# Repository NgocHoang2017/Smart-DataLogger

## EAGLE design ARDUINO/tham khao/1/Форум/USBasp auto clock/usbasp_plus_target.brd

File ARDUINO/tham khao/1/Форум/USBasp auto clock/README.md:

## USBasp with Automatic Software Controlled Clock
---

### Informasi

* __fusebits.txt__ - Pengaturan fusebit untuk ATmega8 untuk USBasp.
* __firmaware.hex__ - Automatic Software Controlled Clock Jumper Free USBasp ATmega8.
* __usbasp_plus_target.sch__ - Skematik untuk USBasp.
* __usbasp_plus_target.brd__ - Layout untuk board USBasp.

### Catatan

* Firmware yang digunakan adalah __Automatic software controlled clock__ sehingga tidak perlu melakukan pengaturan __Low SCK__ lagi.
* Pada layout board USBasp ini terdapat sebuah jalur yang _unrouted_. Cukup abaikan jalur tersebut, karena memang tidak digunakan.
* Board ini telah melalui proses pengujian, dan berfungsi sesuai dengan yang diharapkan.

### Referensi

* [USBasp - USB programmer for Atmel AVR controllers](http://www.fischl.de/usbasp/)
* [Automatic Software Controlled Clock Jumper Free USBasp](https://automasys.wordpress.com/2013/02/16/%D9%BE%D8%B1%D9%88%DA%98%D9%87-%D8%A7%D9%84%DA%A9%D8%AA%D8%B1%D9%88%D9%86%DB%8C%DA%A9-avr-usbasp/)

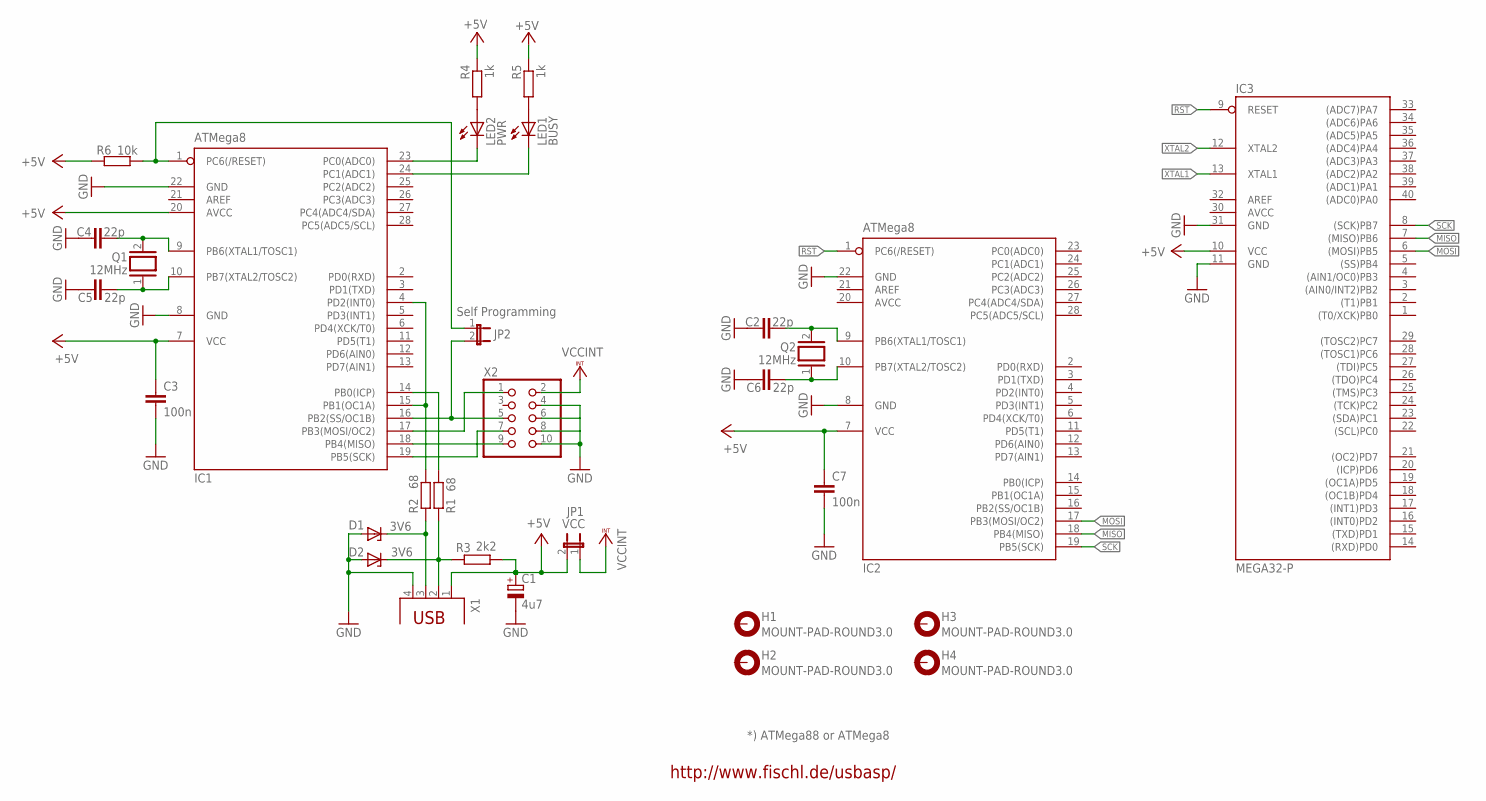
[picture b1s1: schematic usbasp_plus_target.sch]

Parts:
C1: 4u7; E2,5-5
C2, C4, C5, C6: 22p; C025-024X044
C3, C7: 100n; C025-024X044
D1, D2: 3V6; DO34Z7
H1, H2, H3, H4: MOUNT-PAD-ROUND3.0; 3,0-PAD
IC1, IC2: ATMega8; DIL28-3
IC3: MEGA32-P; DIL40
JP1: VCC; JP1
JP2: Self Programming; JP1
LED1: BUSY; LED3MM
LED2: PWR; LED3MM
Q1, Q2: 12MHz; QS
R1, R2: 68; 0204_7
R3: 2k2; 0204_7
R4, R5: 1k; 0204_7
R6: 10k; 0204_7
X1: PN61729
X2: PINHD-2X5; 2X05

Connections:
+5V: C1.+, C3.1, C7.1, IC1.7 (VCC), IC1.20 (AVCC), IC2.7 (VCC), IC3.10 (VCC), JP1.2, R3.1, R4.1, R5.1, R6.1, X1.1
AVCC: IC2.20 (AVCC), IC3.30 (AVCC)
GND: C1.-, C2.1, C3.2, C4.1, C5.1, C6.1, C7.2, D1.A, D2.A, IC1.8 (GND), IC1.22 (GND), IC2.8 (GND), IC2.22 (GND), IC3.11 (GND), IC3.31 (GND), X1.4, X2.4, X2.6, X2.8, X2.10
MISO: IC1.18 (PB4(MISO)), IC2.18 (PB4(MISO)), IC3.7 ((MISO)PB6), X2.9
MOSI: IC1.17 (PB3(MOSI/OC2)), IC2.17 (PB3(MOSI/OC2)), IC3.6 ((MOSI)PB5), X2.1
unnamed: IC1.1 (PC6(/RESET)), JP2.1, R6.2
unnamed: D2.C, R1.1, R3.2, X1.2
unnamed: IC1.4 (PD2(INT0)), IC1.15 (PB1(OC1A)), R2.2
unnamed: D1.C, R2.1, X1.3
unnamed: LED2.A, R4.2
unnamed: IC1.23 (PC0(ADC0)), LED2.K (C)
unnamed: IC1.24 (PC1(ADC1)), LED1.K (C)
unnamed: IC1.14 (PB0(ICP)), R1.2
unnamed: C4.2, IC1.9 (PB6(XTAL1/TOSC1)), Q1.2
unnamed: C5.2, IC1.10 (PB7(XTAL2/TOSC2)), Q1.1
unnamed: LED1.A, R5.2
RST: IC1.16 (PB2(SS/OC1B)), IC2.1 (PC6(/RESET)), IC3.9 (RESET), JP2.2, X2.5
SCK: IC1.19 (PB5(SCK)), IC2.19 (PB5(SCK)), IC3.8 ((SCK)PB7), X2.7
VCCINT: JP1.1, X2.2
XTAL1: C2.2, IC2.9 (PB6(XTAL1/TOSC1)), IC3.13 (XTAL1), Q2.2
XTAL2: C6.2, IC2.10 (PB7(XTAL2/TOSC2)), IC3.12 (XTAL2), Q2.1

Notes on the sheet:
http://www.fischl.de/usbasp/
*) ATMega88 or ATMega8

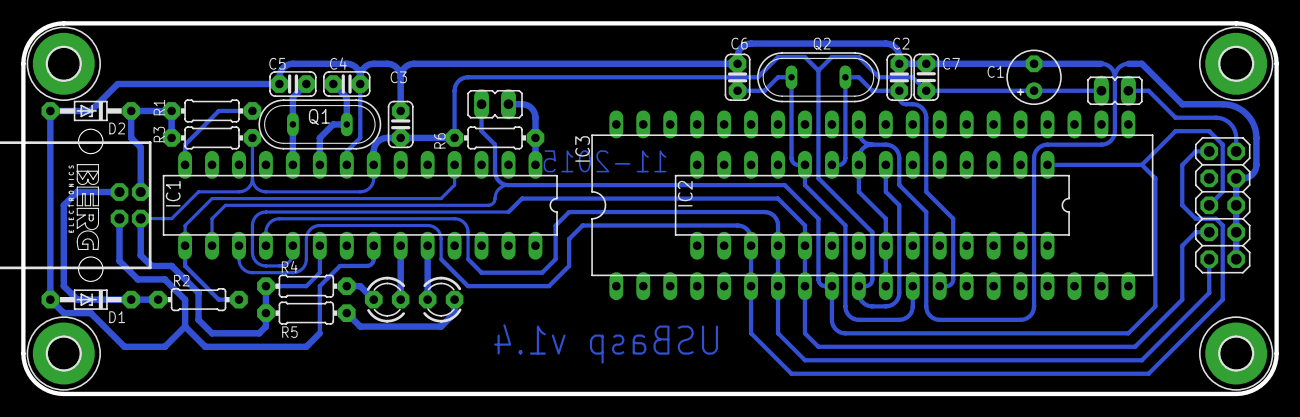
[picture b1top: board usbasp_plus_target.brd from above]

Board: 2 copper layers, 118.1 x 34.9 mm, 30 parts (0 on the bottom side), 21 nets.

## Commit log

2021-11-21 Code update
    code update
